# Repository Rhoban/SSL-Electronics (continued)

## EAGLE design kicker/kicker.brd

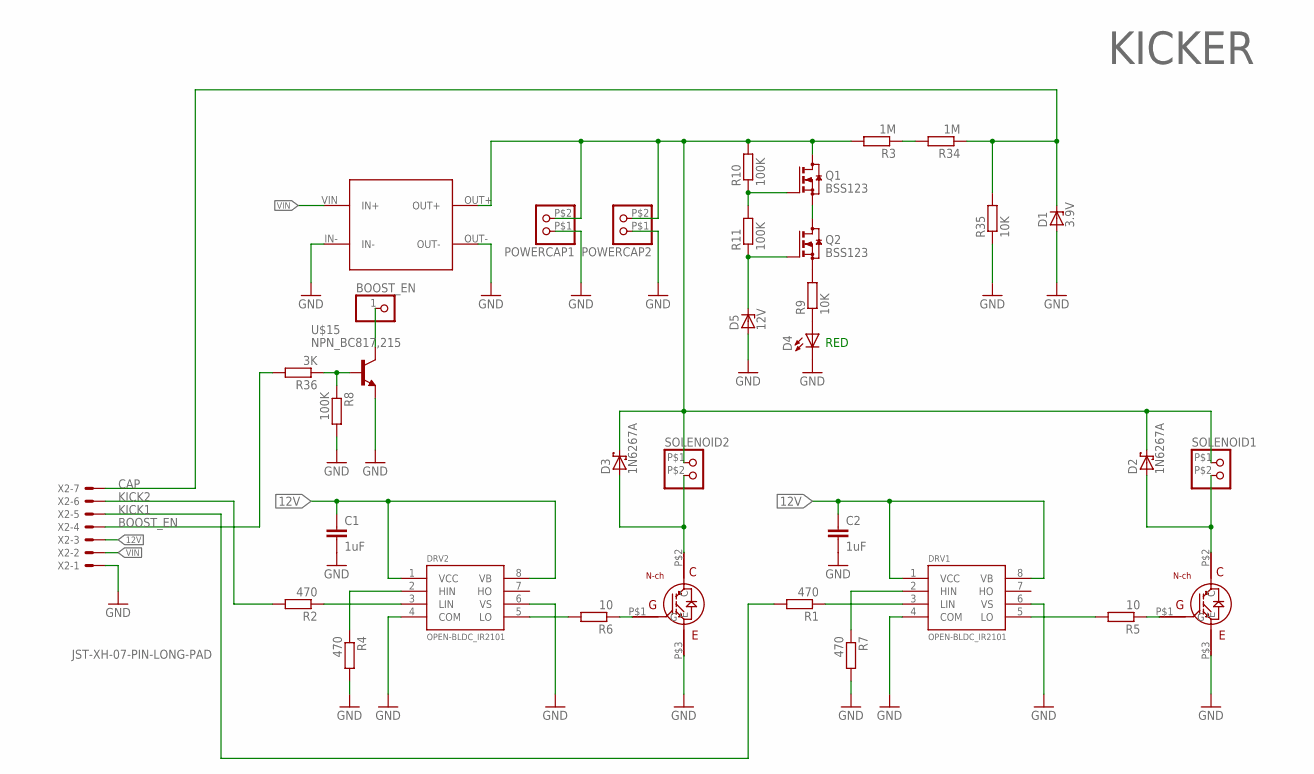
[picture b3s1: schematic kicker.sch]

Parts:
BOOST_EN: CONNEC_1X01
C1, C2: 1uF; C0805
D1: 3.9V; SOD80C; FARNELL 1097198
D2, D3: 1N6267A; C4111-15; FARNELL 9551735
D4: RED; LED-1206; FARNELL 1581233
D5: 12V; SOD80C; FARNELL 2319144
DRV1, DRV2: OPEN-BLDC_IR2101; OPEN-BLDC_SO-8; FARNELL 8638730
POWERCAP1, POWERCAP2: CONNEC_1X02BIG; CONNEC_1X02_BIG
Q1, Q2: BSS123; SOT23
R1, R2, R4, R7: 470; R0805; FARNELL 2446965
R3, R34: 1M; R0805; FARNELL 2129375
R5, R6: 10; R0805; FARNELL 2446965
R8: 100K; R0805; FARNELL 2446965
R9, R35: 10K; R0805; FARNELL 2447553
R10, R11: 100K; R0805; FARNELL 2447553
R36: 3K; R0805; FARNELL 2446965
SOLENOID1, SOLENOID2: CONNEC_1X02BIG; CONNEC_1X02_BIG
U$1, U$11: TO-247A; TO-247; FARNELL 2429705
U$5: BOOSTER; BOOSTER_390V
U$15: NPN_BC817,215; SOT-23; FARNELL 1081223
X2: JST-XH-07-PIN-LONG-PAD; JST-XH-07-PACKAGE-LONG-PAD

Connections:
12V: C1.1, C2.1, DRV1.1 (VCC), DRV1.8 (VB), DRV2.1 (VCC), DRV2.8 (VB), X2.3
BOOST_EN: R36.2, X2.4
CAP: D1.C, R34.1, R35.2, X2.7
GND: C1.2, C2.2, D1.A, D4.C, D5.A, DRV1.4 (COM), DRV1.6 (VS), DRV2.4 (COM), DRV2.6 (VS), POWERCAP1.P$1 (1), POWERCAP2.P$1 (1), R4.2, R7.2, R8.2, R35.1, U$1.P$3 (E), U$5.IN-, U$5.OUT-, U$11.P$3 (E), U$15.2 (E), X2.1
KICK1: R1.2, X2.5
KICK2: R2.2, X2.6
unnamed: DRV2.3 (LIN), R2.1
unnamed: D2.A, SOLENOID1.P$2 (2), U$1.P$2 (C)
unnamed: DRV2.5 (LO), R6.2
unnamed: R3.1, R34.2
unnamed: DRV1.3 (LIN), R1.1
unnamed: DRV2.2 (HIN), R4.1
unnamed: R5.1, U$1.P$1 (G)
unnamed: R6.1, U$11.P$1 (G)
unnamed: DRV1.5 (LO), R5.2
unnamed: Q2.2 (S), R9.2
unnamed: D4.A, R9.1
unnamed: Q1.2 (S), Q2.3 (D)
unnamed: DRV1.2 (HIN), R7.1
unnamed: Q1.1 (G), R10.1, R11.2
unnamed: D5.C, Q2.1 (G), R11.1
unnamed: D3.A, SOLENOID2.P$2 (2), U$11.P$2 (C)
unnamed: BOOST_EN.1, U$15.3 (C)
unnamed: R8.1, R36.1, U$15.1 (B)
VBOOST: D2.C, D3.C, POWERCAP1.P$2 (2), POWERCAP2.P$2 (2), Q1.3 (D), R3.2, R10.2, SOLENOID1.P$1 (1), SOLENOID2.P$1 (1), U$5.OUT+
VIN: U$5.VIN (IN+), X2.2

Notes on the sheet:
KICKER
RED

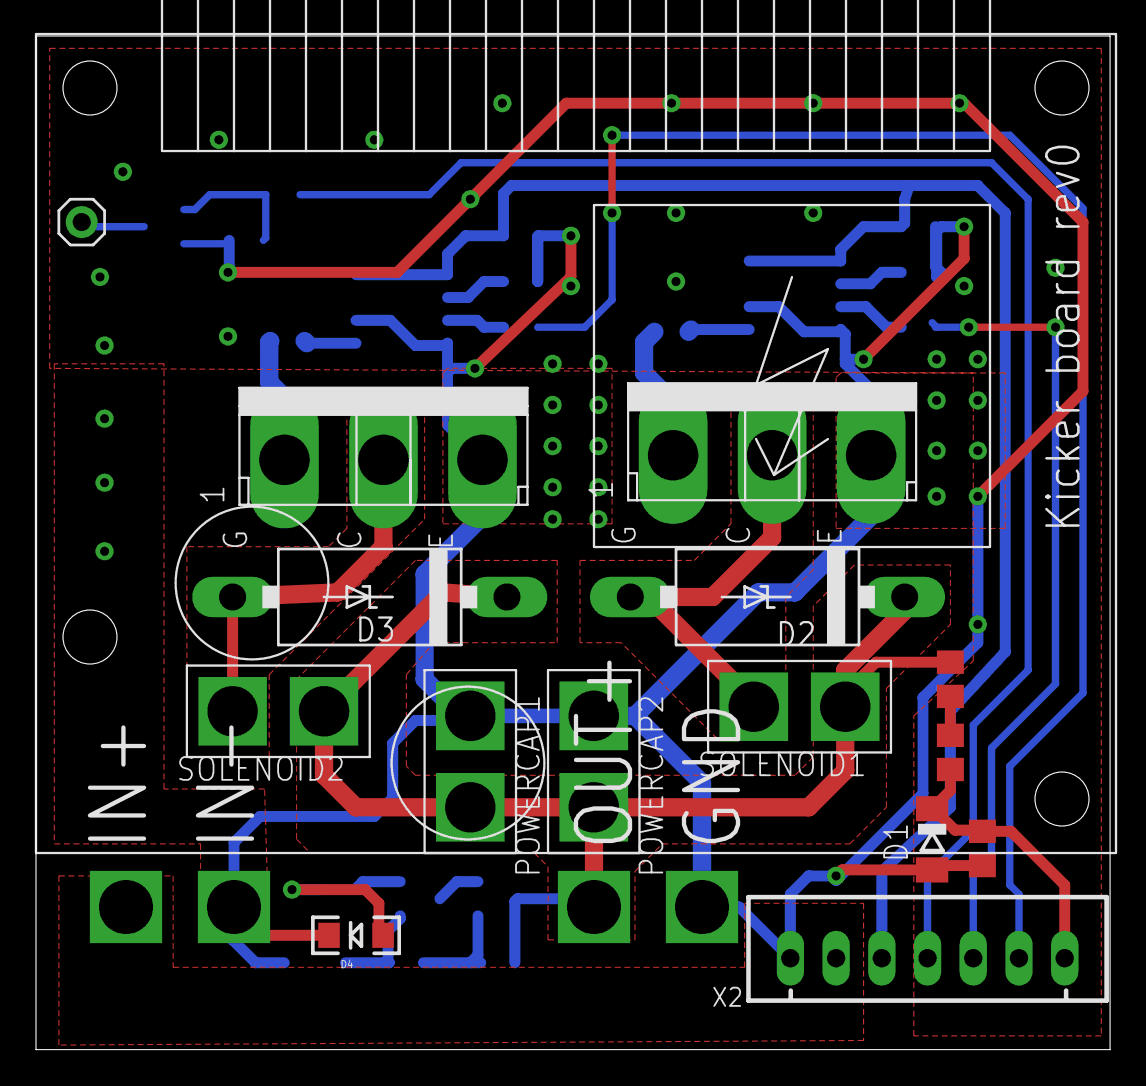
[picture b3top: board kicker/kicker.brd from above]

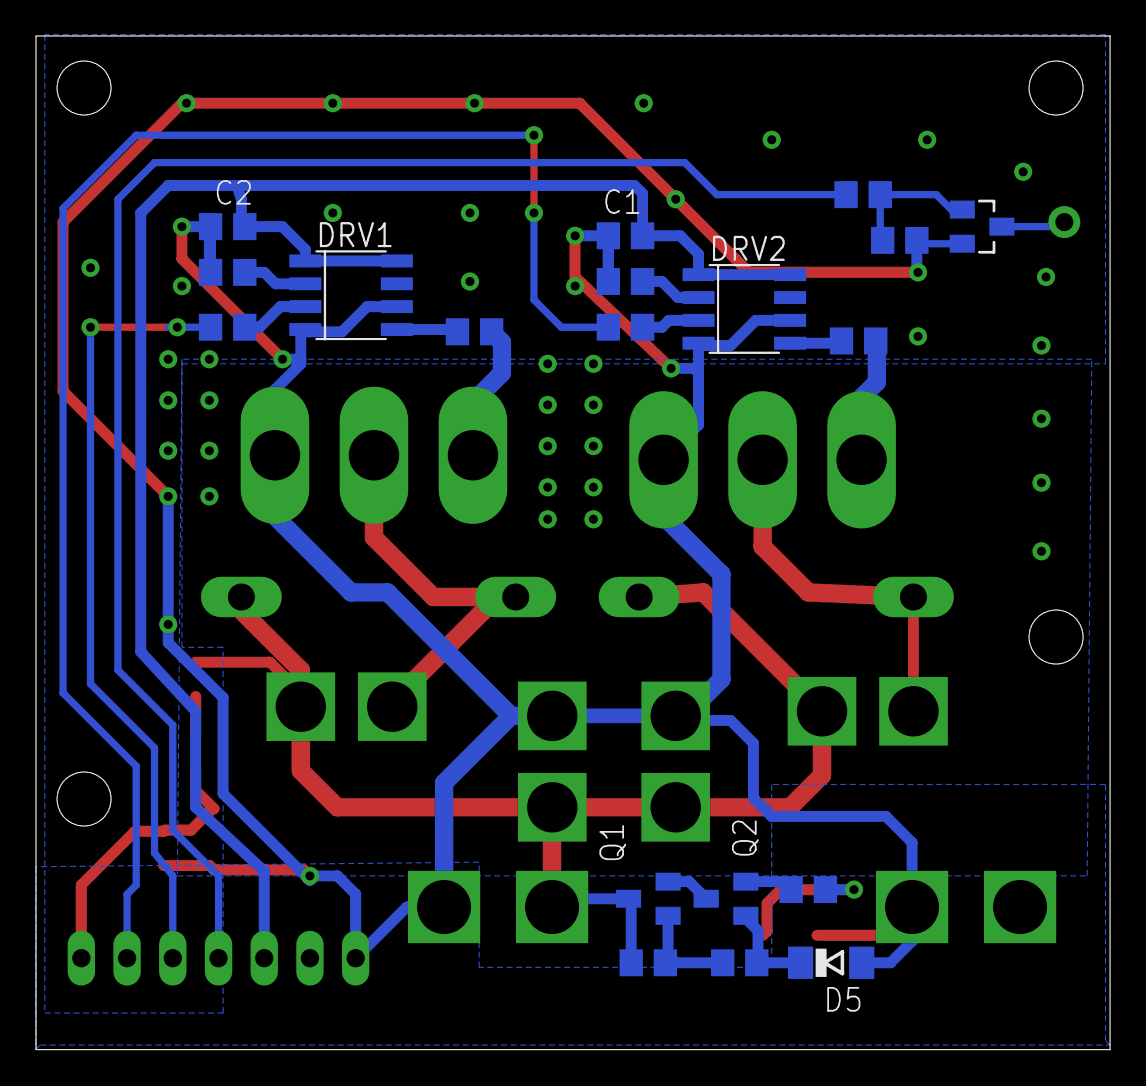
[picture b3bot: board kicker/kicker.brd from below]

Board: 2 copper layers, 59.7 x 56.3 mm, 35 parts (19 on the bottom side), 26 nets.

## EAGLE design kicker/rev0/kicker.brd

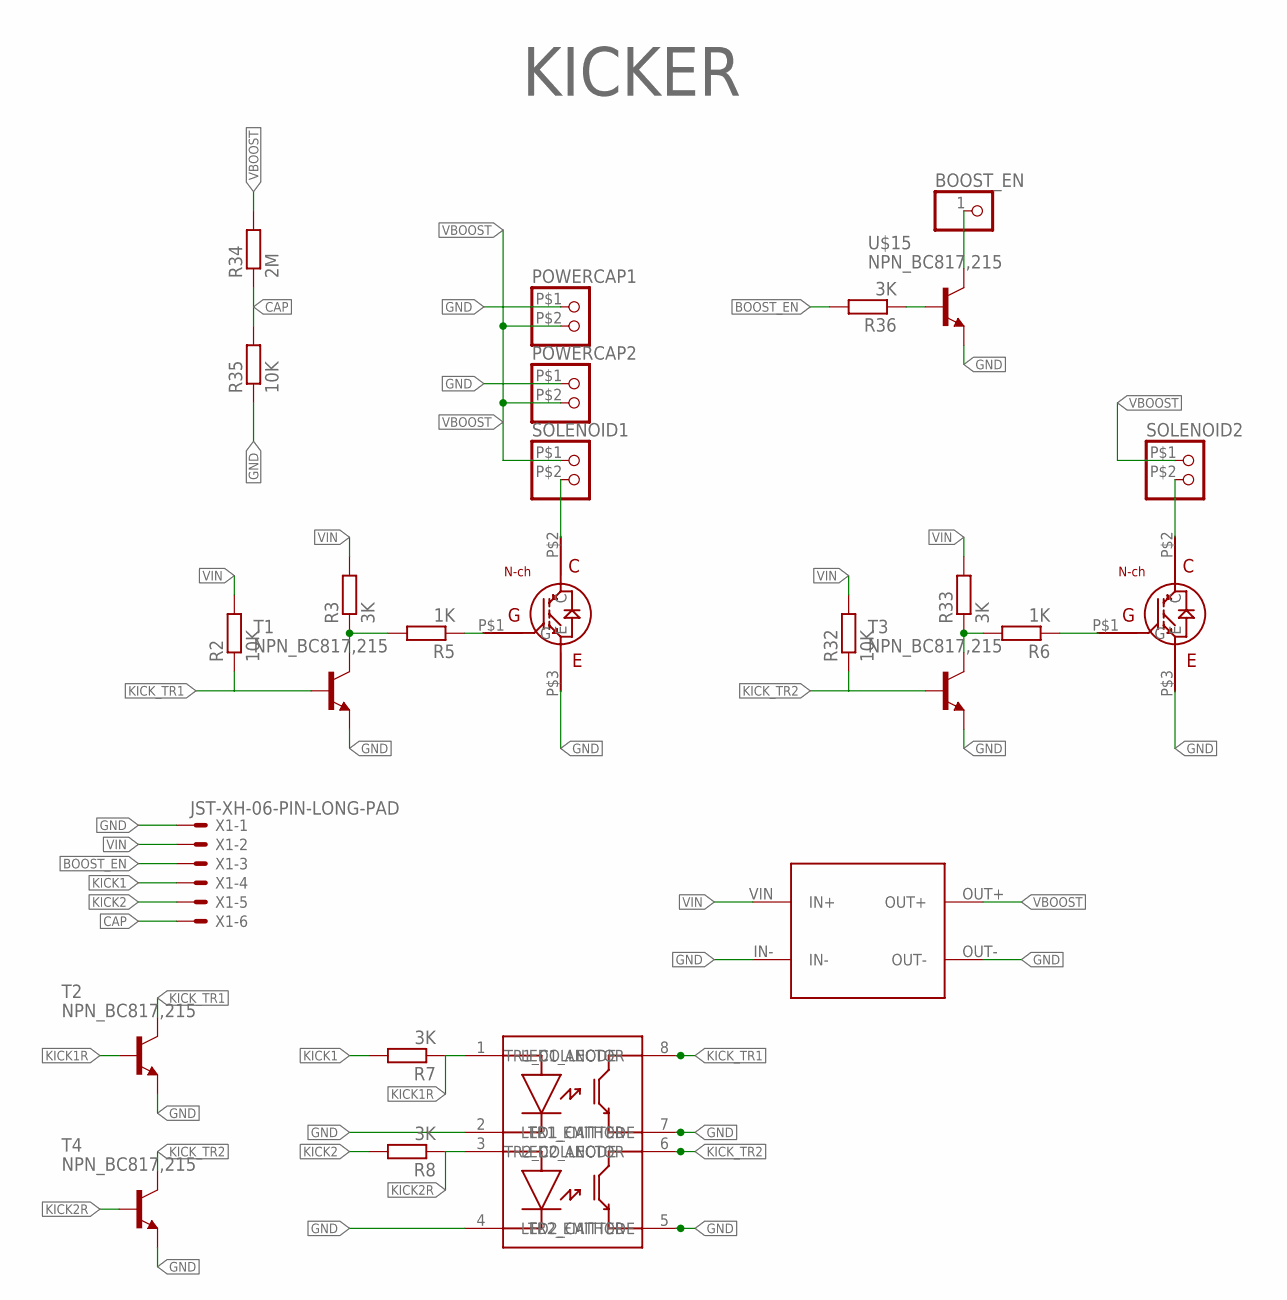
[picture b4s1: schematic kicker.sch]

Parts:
BOOST_EN: CONNEC_1X01
POWERCAP1, POWERCAP2: CONNEC_1X02BIG; CONNEC_1X02_BIG
R2, R32: 10K; R0805; FARNELL 2446965
R3, R7, R8, R33, R36: 3K; R0805; FARNELL 2446965
R5, R6: 1K; R0805; FARNELL 2446965
R34: 2M; R0805; FARNELL 2129375
R35: 10K; R0805; FARNELL 2447553
SOLENOID1, SOLENOID2: CONNEC_1X02BIG; CONNEC_1X02_BIG
T1, T2, T3, T4: NPN_BC817,215; SOT-23; FARNELL 1081223
U$1, U$11: TO-247A; TO-247; FARNELL 2429705
U$4: ACPL-227-500E; SO8; FARNELL 1634749RL
U$5: BOOSTER; BOOSTER_390V
U$15: NPN_BC817,215; SOT-23; FARNELL 1081223
X1: JST-XH-06-PIN-LONG-PAD; JST-XH-06-PACKAGE-LONG-PAD

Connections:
BOOST_EN: R36.2, X1.3
CAP: R34.1, R35.2, X1.6
GND: POWERCAP1.P$1 (1), POWERCAP2.P$1 (1), R35.1, T1.2 (E), T2.2 (E), T3.2 (E), T4.2 (E), U$1.P$3 (E), U$4.2 (LED1_CATHODE), U$4.4 (LED2_CATHODE), U$4.5 (TR2_EMITTER), U$4.7 (TR1_EMITTER), U$5.IN-, U$5.OUT-, U$11.P$3 (E), U$15.2 (E), X1.1
KICK1: R7.2, X1.4
KICK1R: R7.1, T2.1 (B), U$4.1 (LED1_ANODE)
KICK2: R8.2, X1.5
KICK2R: R8.1, T4.1 (B), U$4.3 (LED2_ANODE)
KICK_TR1: R2.1, T1.1 (B), T2.3 (C), U$4.8 (TR1_COLLECTOR)
KICK_TR2: R32.1, T3.1 (B), T4.3 (C), U$4.6 (TR2_COLLECTOR)
unnamed: SOLENOID1.P$2 (2), U$1.P$2 (C)
unnamed: R3.1, R5.2, T1.3 (C)
unnamed: R5.1, U$1.P$1 (G)
unnamed: R6.1, U$11.P$1 (G)
unnamed: R6.2, R33.1, T3.3 (C)
unnamed: SOLENOID2.P$2 (2), U$11.P$2 (C)
unnamed: BOOST_EN.1, U$15.3 (C)
unnamed: R36.1, U$15.1 (B)
VBOOST: POWERCAP1.P$2 (2), POWERCAP2.P$2 (2), R34.2, SOLENOID1.P$1 (1), SOLENOID2.P$1 (1), U$5.OUT+
VIN: R2.2, R3.2, R32.2, R33.2, U$5.VIN (IN+), X1.2

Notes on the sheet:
KICKER

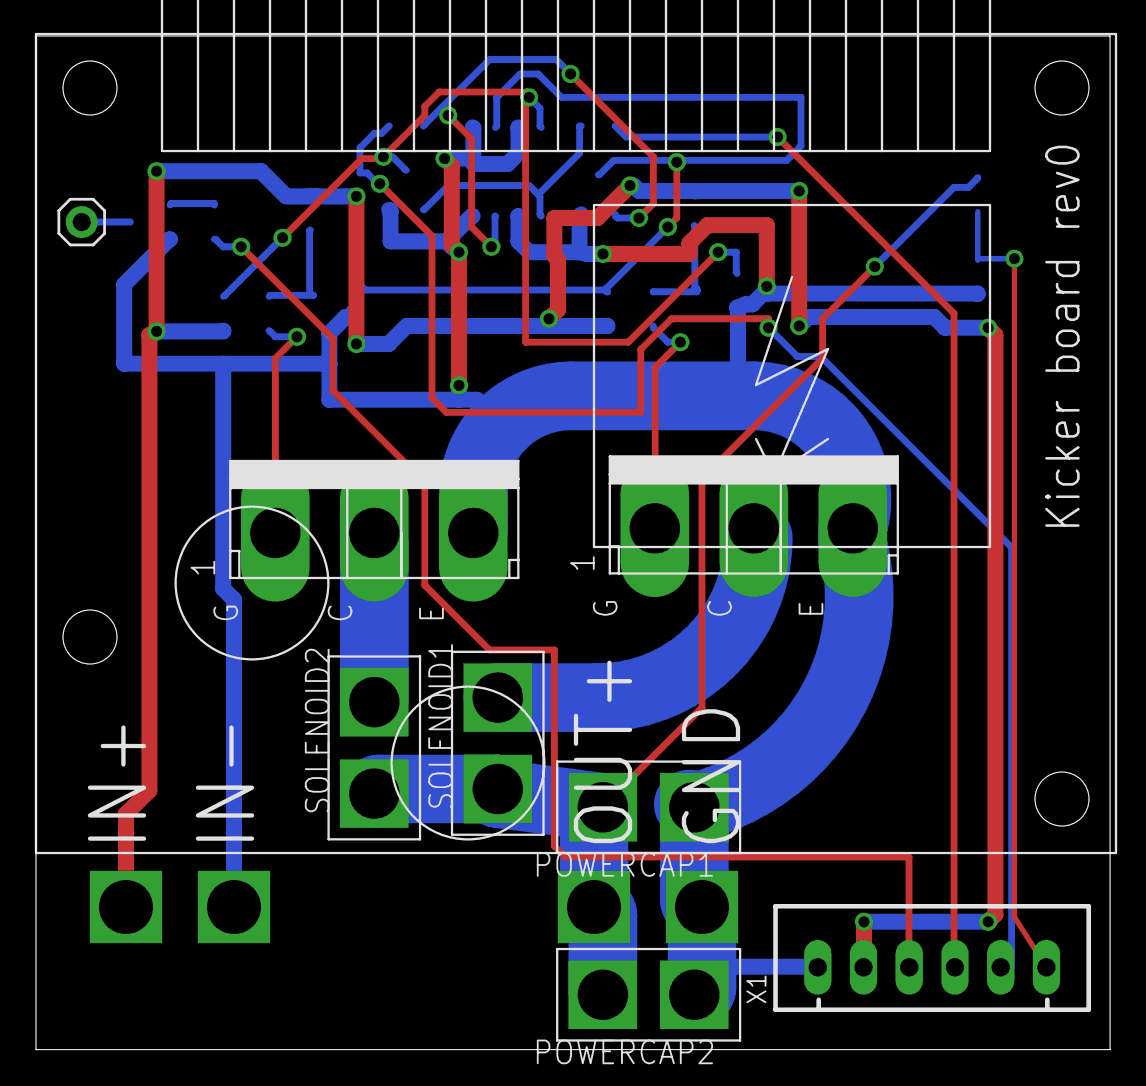
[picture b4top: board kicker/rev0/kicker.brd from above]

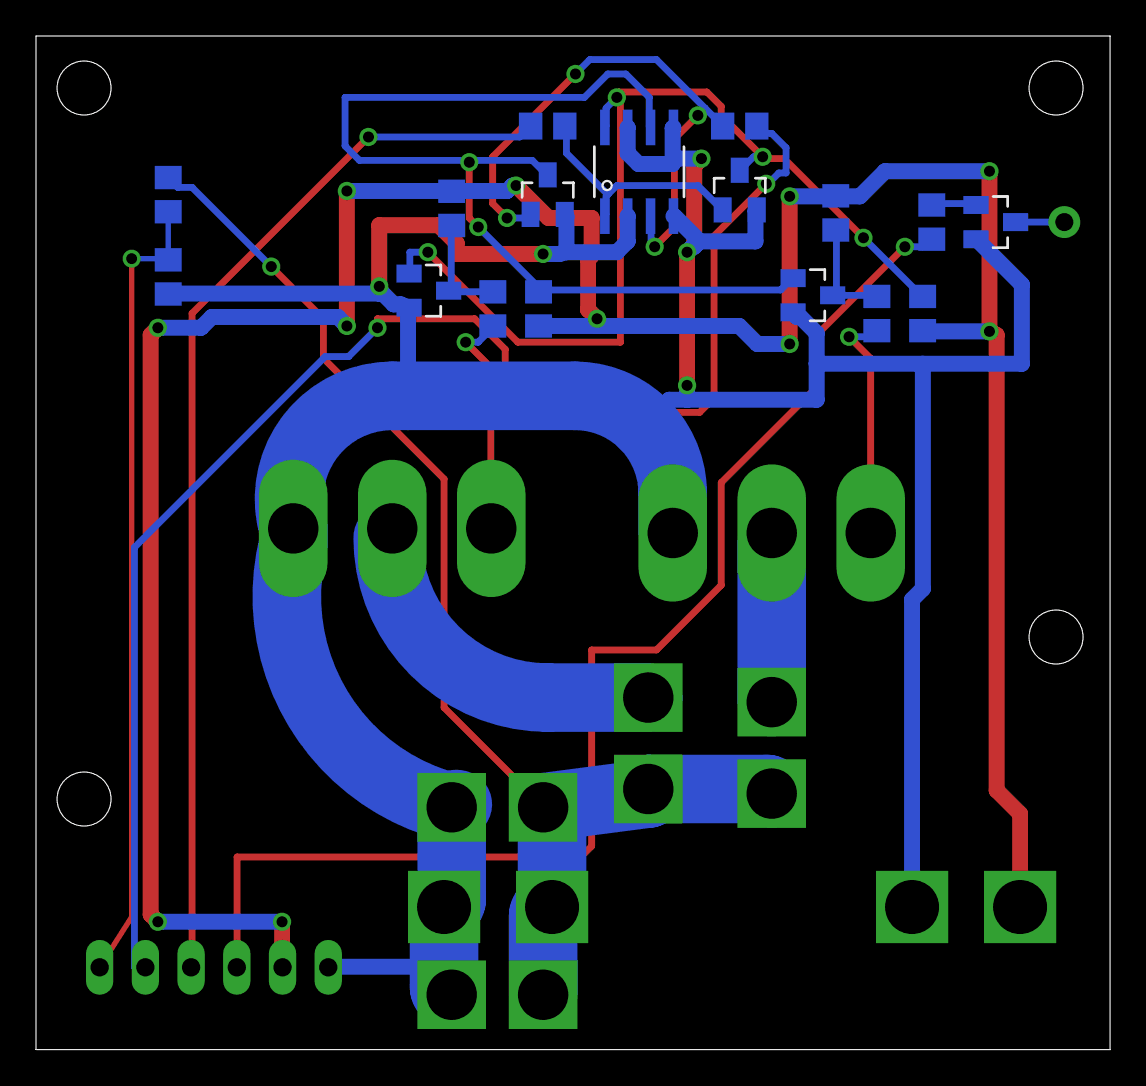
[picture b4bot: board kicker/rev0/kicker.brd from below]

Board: 2 copper layers, 59.7 x 56.3 mm, 26 parts (17 on the bottom side), 19 nets.

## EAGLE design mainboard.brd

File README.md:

# SSL Boards

## Compiling firmware

Be sure you follow the README.md from https://github.com/Rhoban/Maple/ to have the prerequisite.

You can clone the `Maple` repository, for instance in your home:

    git clone git@github.com:Rhoban/Maple.git

Then, go in the firmware directory (for instance in brushless or in mainboard) and make a symlink to it:

    ln -s $HOME/Maple Maple

You can then compile and install:

for master board:
    export COMPILE_MASTER=yes
    export BOOTLOADER_PORT=/dev/ttyACM0
    make clean
    make install

for robot board:
    export COMPILE_MASTER=no
    export BOOTLOADER_PORT=/dev/ttyACM0
    make clean
    make install

-------------------------------------------------

## Components

You can find most of the component source in the `FARNELL` attribute of each component.

### Main board

### Connectors

* JST-ZH 2 pin connector + cables
* JST-XH 7 pins connector for kicker board
* XT-60 connector (same as wire connector)

#### Maple mini

Board containing micro-controller (mainboard controller)

#### GY-85

9DOF IMU

#### nRF24L01 modules

2.4Ghz communication modules with short antenna (Farnell: 2143316)

### Screws

* M3 holes are on the board, on a 126x82mm rectangle.
* M3x10 spacers can be used to hold the drivers on the board

-------------------------------------------------

## Brushless driver

### Connectors

* JST-ZH 5 pin connector (for hall sensor)
* JST-ZH 6 pin connector (for encoder)
* JST-XH 3 pin connector (for motor phases)
  
-------------------------------------------------

## Kicker board

### Power capacitor

Power capacitors, current target is 2200uF / 200V (2102441)

### Flash brushless driver
first, add a udev rules in /etc/udev/rules.d/10-maple.rules 

ATTRS{idProduct}=="0003", ATTRS{idVendor}=="1eaf", MODE="0666", GROUP="plugdev" SYMLINK+="maple"

in brushless/firmware directory
   make
Then, with robot off and usb cable connected to driver (connector under the robot), enter the following command
just after plug-in:

dfu-util -a1 -d 1eaf:0003 -D build/maple.bin  -d /dev/maple

This is because driver remains in dfu only a short time after power up. If it fails, try again

### Connectors

* JST-XH 7 pins connector

#### Voltage booster

Can be easily found with keywords "390V booster"

### Screws

M3 spacers to fix the board

-------------------------------------------------

## Misc

#### Fuses

F447 fuses on the wire are used to protect

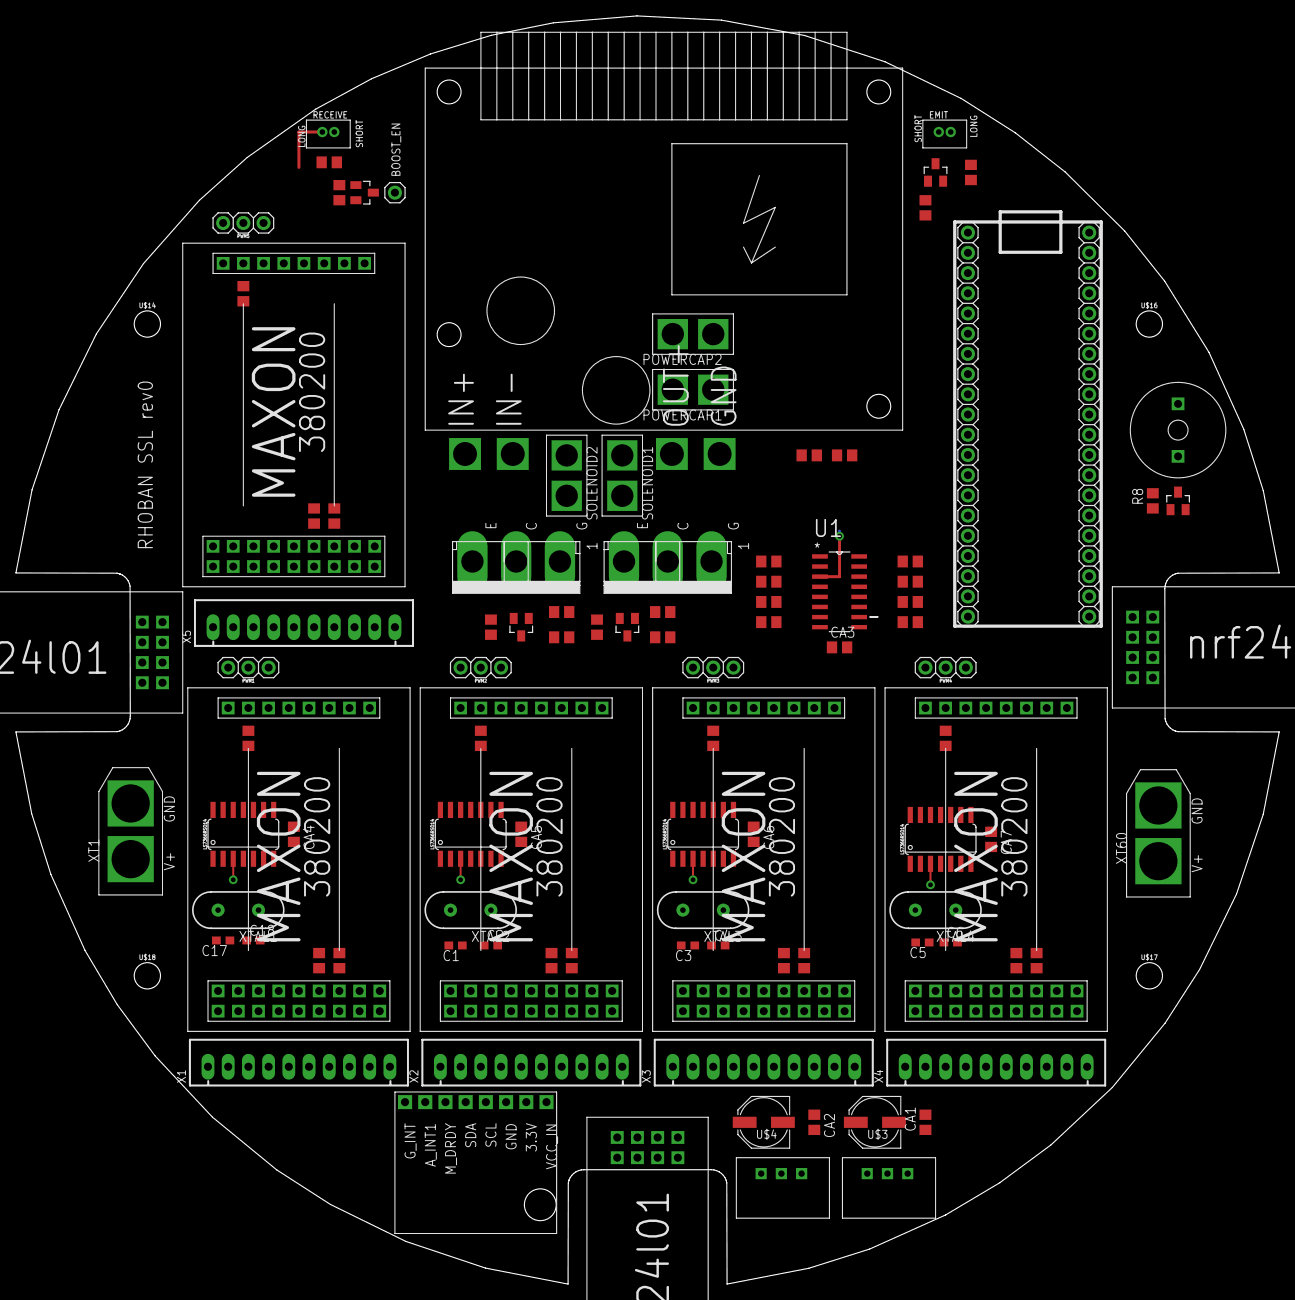
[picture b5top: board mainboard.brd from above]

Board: 2 copper layers, 158.8 x 159.4 mm, 106 parts (0 on the bottom side), 116 nets.

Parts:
BOOST_EN: CONNEC_1X01
C1, C2, C3, C4, C5, C6, C17, C18: 15pF; C0603
CA1, CA2, CA3, CA4, CA5, CA6, CA7: C_EU-100NF; C0805
COM1, COM2, COM3: NRF24L01
EMIT: CONNEC_1X02JST-ZH; JST_ZH_2P
ENC1, ENC2, ENC3, ENC4: LS7366RSO14; SO14
MAPLE: MAPLE_MINI; CONNEC_2X20
POWERCAP1, POWERCAP2: CONNEC_1X02BIG; CONNEC_1X02_BIG
PWM1, PWM2, PWM3, PWM4, PWM5: CONNEC_1X03
R1, R4, R16, R17, R19, R20, R22, R23, R25, R26, R28, R29, R31: 1K; R0805
R2, R3, R7, R8, R9, R10, R11, R12, R13, R14, R15, R32, R33, R36: 3K; R0805
R5: 110; R0805
R6, R35: 10K; R0805
R18, R21, R24, R27, R30: 24k; R0805
R34: 2M; R0805
RECEIVE: CONNEC_1X02JST-ZH; JST_ZH_2P
REG3.3V, REG5V: REG_5V; TRACOPOWER
SOLENOID1, SOLENOID2: CONNEC_1X02BIG; CONNEC_1X02_BIG
T1, T2, T3: NPN_BC817,215; SOT-23
U1: CD4051BM; SOIC127P600X175-16N
U$1, U$11: TO-247A; TO-247
U$2: GY-85
U$3, U$4: 47uF; PANASONIC_D
U$5: BOOSTER; BOOSTER_390V
U$6, U$7, U$8, U$9, U$10: MAXON380200
U$12, U$15: NPN_BC817,215; SOT-23
U$13: BUZZER66
U$14, U$16, U$17, U$18: STAND-OFF
X1, X2, X3, X4, X5: JST-XH-10-PIN-LONG-PAD; JST-XH-10-PACKAGE-LONG-PAD
XT1, XT60: CONNEC_ALIM; XT60
XTAL1, XTAL2, XTAL3, XTAL4: 40Mhz; HC49US

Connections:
3.3: CA1.1, CA3.1, COM1.CE, COM1.VCC, COM2.CE, COM2.VCC, COM3.CE, COM3.VCC, MAPLE.AV+, MAPLE.VCC, R2.2, R6.1, R7.1, R9.1, R10.1, R11.1, R12.1, R13.1, R14.1, R15.1, R32.2, REG3.3V.P$3, U1.16, U$2.3.3, U$3.+, U$13.P$2
BOOST_EN: MAPLE.X27, R36.2
BUZZER: MAPLE.X11, R8.2
CAP: MAPLE.X6, R34.1, R35.2
CS1: ENC1.4, R7.2, U1.13
CS2: ENC2.4, R9.2, U1.14
CS3: ENC3.4, R10.2, U1.15
CS4: ENC4.4, R11.2, U1.12
CS5: COM1.CSN, R12.2, U1.1
CS6: COM2.CSN, R13.2, U1.5
CS7: COM3.CSN, R14.2, U1.2
CS8: R15.2, U1.4
CSA1: MAPLE.X20, U1.11
CSA2: MAPLE.X21, U1.10
CSA3: MAPLE.X22, U1.9
GND: C1.1, C2.1, C3.1, C4.1, C5.1, C6.1, C17.1, C18.1, CA1.2, CA2.2, CA3.2, CA4.2, CA5.2, CA6.2, CA7.2, COM1.GND, COM2.GND, COM3.GND, ENC1.3, ENC2.3, ENC3.3, ENC4.3, MAPLE.AV-, MAPLE.GND, POWERCAP1.P$1, POWERCAP2.P$1, PWM1.1, PWM2.1, PWM3.1, PWM4.1, PWM5.1, R16.1, R18.1, R19.1, R21.1, R22.1, R24.1, R25.1, R27.1, R28.1, R30.1, R35.1, RECEIVE.P$2, T1.2, T2.2, T3.2, U1.3, U1.6, U1.7, U1.8, U$1.P$3, U$2.GND, U$3.-, U$4.-, U$5.IN-, U$5.OUT-, U$6.9, U$6.10, U$6.14, U$6.16, U$6.24, U$7.9, U$7.10, U$7.14, U$7.16, U$7.24, U$8.9, U$8.10, U$8.14, U$8.16, U$8.24, U$9.9, U$9.10, U$9.14, U$9.16, U$9.24, U$10.9, U$10.10, U$10.14, U$10.16, U$10.24, U$11.P$3, U$12.2, U$15.2, X1.4, X2.4, X3.4, X4.4, X5.4, XT1.GND, XT60.GND
IMU_SCL: MAPLE.X16, U$2.SCL
IMU_SDA: MAPLE.X15, U$2.SDA
INDEX: ENC1.10, ENC2.10, ENC3.10, ENC4.10, MAPLE.X26
IRQ1: COM1.IRQ, MAPLE.X23
IRQ2: COM2.IRQ, MAPLE.X24
IRQ3: COM3.IRQ, MAPLE.X25
IR_EMIT: MAPLE.X12, R4.1
IR_RECEIVE: MAPLE.X10, R6.2, RECEIVE.P$1
KICK1: MAPLE.X0, R1.1, R2.1
KICK2: MAPLE.X1, R31.1, R32.1
M1_A: ENC1.12, X1.9
M1_B: ENC1.11, X1.10
M1_DIR: MAPLE.X13, U$6.23
M1_HALL1: U$6.13, X1.6
M1_HALL2: U$6.15, X1.7
M1_HALL3: U$6.17, X1.8
M1_SPEED: MAPLE.X3, PWM1.3, U$6.26
M1_W1: U$6.1, U$6.2, X1.1
M1_W2: U$6.3, U$6.4, X1.2
M1_W3: U$6.5, U$6.6, X1.3
M2_A: ENC2.12, X2.9
M2_B: ENC2.11, X2.10
M2_DIR: MAPLE.X14, U$7.23
M2_HALL1: U$7.13, X2.6
M2_HALL2: U$7.15, X2.7
M2_HALL3: U$7.17, X2.8
M2_SPEED: MAPLE.X4, PWM2.3, U$7.26
M2_W1: U$7.1, U$7.2, X2.1
M2_W2: U$7.3, U$7.4, X2.2
M2_W3: U$7.5, U$7.6, X2.3
M3_A: ENC3.12, X3.9
M3_B: ENC3.11, X3.10
M3_DIR: MAPLE.X17, U$8.23
M3_HALL1: U$8.13, X3.6
M3_HALL2: U$8.15, X3.7
M3_HALL3: U$8.17, X3.8
M3_SPEED: MAPLE.X5, PWM3.3, U$8.26
M3_W1: U$8.1, U$8.2, X3.1
M3_W2: U$8.3, U$8.4, X3.2
M3_W3: U$8.5, U$8.6, X3.3
M4_A: ENC4.12, X4.9
M4_B: ENC4.11, X4.10
M4_DIR: MAPLE.X18, U$9.23
M4_HALL1: U$9.13, X4.6
M4_HALL2: U$9.15, X4.7
M4_HALL3: U$9.17, X4.8
M4_SPEED: MAPLE.X8, PWM4.3, U$9.26
M4_W1: U$9.1, U$9.2, X4.1
M4_W2: U$9.3, U$9.4, X4.2
M4_W3: U$9.5, U$9.6, X4.3
M5_DIR: MAPLE.X19, U$10.23
M5_HALL1: U$10.13, X5.6
M5_HALL2: U$10.15, X5.7
M5_SPEED: MAPLE.X9, PWM5.3, U$10.26
M5_W1: U$10.1, U$10.2, X5.1
M5_W2: U$10.3, U$10.4, X5.2
M5_W3: U$10.5, U$10.6, X5.3
MISO: COM1.MISO, COM2.MISO, COM3.MISO, ENC1.6, ENC2.6, ENC3.6, ENC4.6, MAPLE.X29
MOSI: COM1.MOSI, COM2.MOSI, COM3.MOSI, ENC1.7, ENC2.7, ENC3.7, ENC4.7, MAPLE.X28
MOTORS_EN: U$6.22, U$7.22, U$8.22, U$9.22, U$10.22
unnamed: R1.2, T1.1
unnamed: SOLENOID1.P$2, U$1.P$2
unnamed: R8.1, U$12.1
unnamed: R3.1, T1.3, U$1.P$1
unnamed: U$12.3, U$13.P$1
unnamed: EMIT.P$1, R5.2
unnamed: EMIT.P$2, T2.3
unnamed: R16.2, U$6.20
unnamed: R4.2, T2.1
unnamed: R17.2, U$6.21
unnamed: C1.2, ENC2.1, XTAL2.2
unnamed: C2.2, ENC2.2, XTAL2.1
unnamed: R19.2, U$7.20
unnamed: R18.2, U$6.25
unnamed: R31.2, T3.1
unnamed: R20.2, U$7.21
unnamed: C17.2, ENC1.1, XTAL1.2
unnamed: C18.2, ENC1.2, XTAL1.1
unnamed: R21.2, U$7.25
unnamed: C3.2, ENC3.1, XTAL3.2
unnamed: C4.2, ENC3.2, XTAL3.1
unnamed: R22.2, U$8.20
unnamed: R23.2, U$8.21
unnamed: R24.2, U$8.25
unnamed: C5.2, ENC4.1, XTAL4.2
unnamed: C6.2, ENC4.2, XTAL4.1
unnamed: R25.2, U$9.20
unnamed: R26.2, U$9.21
unnamed: R27.2, U$9.25
unnamed: R28.2, U$10.20
unnamed: R29.2, U$10.21
unnamed: R30.2, U$10.25
unnamed: R33.1, T3.3, U$11.P$1
unnamed: SOLENOID2.P$2, U$11.P$2
unnamed: BOOST_EN.1, U$15.3
unnamed: R36.1, U$15.1
SCK: COM1.SCK, COM2.SCK, COM3.SCK, ENC1.5, ENC2.5, ENC3.5, ENC4.5, MAPLE.X30
VBOOST: POWERCAP1.P$2, POWERCAP2.P$2, R34.2, SOLENOID1.P$1, SOLENOID2.P$1, U$5.OUT+
VCC: CA2.1, CA4.1, CA5.1, CA6.1, CA7.1, ENC1.14, ENC2.14, ENC3.14, ENC4.14, R17.1, R20.1, R23.1, R26.1, R29.1, REG5V.P$3, U$4.+, U$6.11, U$7.11, U$8.11, U$9.11, U$10.11, X1.5, X2.5, X3.5, X4.5, X5.5
VIN: R3.2, R5.1, R33.2, REG3.3V.P$1, REG5V.P$1, U$5.VIN, U$6.7, U$6.8, U$7.7, U$7.8, U$8.7, U$8.8, U$9.7, U$9.8, U$10.7, U$10.8, XT1.V+, XT60.V+

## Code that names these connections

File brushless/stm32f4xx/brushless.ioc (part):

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Mcu.Name=STM32F401R(B-C)Tx
Mcu.Package=LQFP64
Mcu.UserName=STM32F401RBTx
PA10.GPIOParameters=GPIO_Label
PA10.GPIO_Label=WPWM
PA10.Signal=S_TIM1_CH3
PA11.GPIOParameters=GPIO_Label
PA11.GPIO_Label=USB_DM
PA11.Mode=Device_Only
PA11.Signal=USB_OTG_FS_DM
PA12.GPIOParameters=GPIO_Label
PA12.GPIO_Label=USB_DP
PA12.Mode=Device_Only
PA12.Signal=USB_OTG_FS_DP
PA13.Mode=JTAG_4_pins
PA13.Signal=SYS_JTMS-SWDIO
PA14.Mode=JTAG_4_pins
PA14.Signal=SYS_JTCK-SWCLK
PA15.Mode=JTAG_4_pins
PA15.Signal=SYS_JTDI
PA5.Signal=S_TIM2_CH1_ETR
PA7.Signal=S_TIM3_CH2
PA8.GPIOParameters=GPIO_Label
PA8.GPIO_Label=UPWM
PA8.Signal=S_TIM1_CH1
PA9.GPIOParameters=GPIO_Label
PA9.GPIO_Label=VPWM
PA9.Signal=S_TIM1_CH2
PB1.GPIOParameters=GPIO_Label
PB1.GPIO_Label=LED
PB1.Signal=GPIO_Output
PB12.GPIOParameters=GPIO_Speed,PinState,GPIO_Label
PB12.GPIO_Label=ENC_INT_CS
PB12.GPIO_Speed=GPIO_SPEED_FREQ_VERY_HIGH
PB12.PinState=GPIO_PIN_SET
PB12.Signal=GPIO_Output
PB13.GPIOParameters=GPIO_Label
PB13.GPIO_Label=ENC_SCK
PB13.Mode=Full_Duplex_Master
PB13.Signal=SPI2_SCK
PB14.GPIOParameters=GPIO_Label
PB14.GPIO_Label=ENC_MISO
PB14.Mode=Full_Duplex_Master
PB14.Signal=SPI2_MISO
PB15.GPIOParameters=GPIO_Label
PB15.GPIO_Label=ENC_MOSI
PB15.Mode=Full_Duplex_Master
PB15.Signal=SPI2_MOSI
PB3.Mode=JTAG_4_pins
PB3.Signal=SYS_JTDO-SWO
PC0.GPIOParameters=GPIO_Label
PC0.GPIO_Label=I_U
PC0.Signal=ADCx_IN10
PC1.GPIOParameters=GPIO_Label
PC1.GPIO_Label=I_W
PC1.Signal=ADCx_IN11
PC14-OSC32_IN.Mode=LSE-External-Oscillator
PC14-OSC32_IN.Signal=RCC_OSC32_IN
PC15-OSC32_OUT.Mode=LSE-External-Oscillator
PC15-OSC32_OUT.Signal=RCC_OSC32_OUT
PC2.GPIOParameters=GPIO_Label
PC2.GPIO_Label=I_REF
PC2.Signal=ADCx_IN12
PC3.GPIOParameters=GPIO_Label
PC3.GPIO_Label=I_V
PC3.Signal=ADCx_IN13
PC6.GPIOParameters=GPIO_Label
PC6.GPIO_Label=UEN
PC6.Signal=GPIO_Output
PC7.GPIOParameters=GPIO_Label
PC7.GPIO_Label=VEN
PC7.Signal=GPIO_Output
PC8.GPIOParameters=GPIO_Label
PC8.GPIO_Label=WEN
PC8.Signal=GPIO_Output
PC9.GPIOParameters=GPIO_Speed,PinState,GPIO_Label
PC9.GPIO_Label=ENC_EXT_CS
PC9.GPIO_Speed=GPIO_SPEED_FREQ_VERY_HIGH
PC9.PinState=GPIO_PIN_SET
PC9.Signal=GPIO_Output
PH0\ -\ OSC_IN.Mode=HSE-External-Oscillator
PH0\ -\ OSC_IN.Signal=RCC_OSC_IN
PH1\ -\ OSC_OUT.Mode=HSE-External-Oscillator
PH1\ -\ OSC_OUT.Signal=RCC_OSC_OUT
RCC.HSE_VALUE=8000000
RCC.SYSCLKFreq_VALUE=84000000
RCC.SYSCLKSource=RCC_SYSCLKSOURCE_PLLCLK
board=custom

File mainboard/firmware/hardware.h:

#ifndef _HARDWARE_H
#define _HARDWARE_H

#include <stdint.h>

#define GREG 1
#define CATIE 2

#ifdef CATIE_BOARD
  #define BOARD CATIE
#endif
#ifdef GREG_BOARD
  #define BOARD GREG
#endif
#ifndef BOARD
  static_assert(false);
#endif

// Brushless drivers
#define DRIVERS_CS1 7
#define DRIVERS_CS2 1
#define DRIVERS_CS3 19
#define DRIVERS_CS4 18
#define DRIVERS_CS5 17

#define DRIVERS_SPI 1

// Multiplexer
#define MUX         8

#define ADDR1       14
#define ADDR2       31
#define ADDR3       2

// Communication pins
#define COM_CE1  13
#define COM_CE2  3
#define COM_CE3  9

#define COM_CS1 20
#define COM_CS2 21
#define COM_CS3 22

#define COM_IRQ1 23
#define COM_IRQ2 24
#define COM_IRQ3 0

#define COM_SPI 2

// Communication configuration
#define COM_ADDR   {0x22, 0x87, 0xe8, 0xf9, 0x00}
#define COM_MASTER 0xff

// Buzzer
#define BUZZER_PIN      11
#define BUZZER_TIMER    2

// Booster
#define BOOSTER_PIN     27
#define BOOSTER_TIMER   1
#define CAP_ADDR        4
#define CAP_R1          200000.0
#define CAP_R2          2000.0
#define CHARGE_CUR_ADDR 6
#define KICKER_CHARGING_VALUE 150.0

// Hall sensor
#define HALL1_ADDR      0
#define HALL2_ADDR      1
#define HALL3_ADDR      2
#define HALL4_ADDR      3

#define HALL_THRES     2000

// Kicker
#define KICKER1_PIN     25
#define KICKER2_PIN     26
#define KICKER_TIMER    4

// Voltage
#define BAT_ADDR        5
#define BAT_R1          10000
#define BAT_R2          1000

// Infrared
#define IR_EMIT         12
#define IR_RECEIVE      10
#define IR_THRESHOLD    600

void get_uid(uint8_t id[12]);

#endif

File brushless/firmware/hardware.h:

#ifndef _HARDWARE_H
#define _HARDWARE_H

#include "ssl.h"

// Flash address to write/read infos
#define INFO_FLASH_ADDR    0x0801FC00


// Defines the driver type (see below)
#define DRIVER_TYPE     TYPE_70W

#define TYPE_30W        1
#define TYPE_70W        2
#define TYPE_DRIBBLER   3

#ifndef DRIVER_TYPE
#error "You should set a value for DRIVER_TYPE"
#endif

// Encoder configuration
#if DRIVER_TYPE == TYPE_30W
#define ENCODER_QUADRATURE          // Quadrature encoder A/B
#define ENCODER_CPR      1024
#endif

#if DRIVER_TYPE == TYPE_70W
#define ENCODER_MAGNETIC            // Magnetic AS5048 14bit encoder
// #define ENCODER_CPR      1024
#define ENCODER_CPR      16384
// #define ENCODER_NONE                // No encoder
#endif

#if DRIVER_TYPE == TYPE_DRIBBLER
#define ENCODER_NONE                // No encoder
#endif

#define GREG 1
#define CATIE 2

#ifdef CATIE_BOARD
  #define BOARD CATIE
#endif
#ifdef GREG_BOARD
  #define BOARD GREG
#endif
#ifndef BOARD
  static_assert(false);
#endif

#if BOARD == CATIE
  #define REVERSE_HALL_PHASE
  // For SPI based encoders
  #define ENCODER_SPI         2
  #define ENCODER_SELECT_PIN  PB12
  #define ENCODER_SELECT_PIN_2  PC9
  #define ENCODER_INDEX_PIN   12 // Used to make a shift bit to define PB12

  // Current sensing
  #define CURRENT_U_PIN      PC0
  #define CURRENT_V_PIN      PC3
  #define CURRENT_W_PIN      PC1
  #define CURRENT_REF_PIN      PC2

  // Motors pins

  #ifdef REVERSE_PHASE
      #define U_SD_PIN       PC6  //use Timer 1 (Maple)
      #define U_IN_PIN       PA8  //use Timer 1 (Maple)

      #define V_SD_PIN       PC8  //use Timer 1 (Maple)
      #define V_IN_PIN       PA10  //use Timer 1 (Maple)

#define W_SD_PIN       PC7 //use Timer 1 (Maple)
#define W_IN_PIN       PA9 //use Timer 1 (Maple)
  #else
      #define U_SD_PIN       PC6 //use Timer 1 (Maple)
      #define U_IN_PIN       PA8 //use Timer 1 (Maple)

      #define V_SD_PIN       PC7 //use Timer 1 (Maple)
      #define V_IN_PIN       PA9 //use Timer 1 (Maple)

      #define W_SD_PIN       PC8  //use Timer 1 (Maple)
      #define W_IN_PIN       PA10 //use Timer 1 (Maple)
  #endif



  #ifdef REVERSE_HALL_PHASE
    #define HALLU_PIN        PA0
    #define HALLW_PIN        PA1
    #define HALLV_PIN        PA2
  #else
    #define HALLU_PIN        PA0
    #define HALLV_PIN        PA1
    #define HALLW_PIN        PA2
  #endif

  // SPI slave pin
  #define SLAVE_SPI           1
  #define SLAVE_PIN PA4
  #define SLAVE_CLK_PIN PA5
  #define SLAVE_MISO_PIN PA6
  #define SLAVE_MOSI_PIN PA7

  // Board LED pin
  #define LED_PIN     PB1
#endif

#if BOARD == GREG
  // For SPI based encoders
  #define ENCODER_SPI         2
  #define ENCODER_SELECT_PIN  31
  #define ENCODER_INDEX_PIN   12

  // Current sensing
  #define CURRENT_PIN      4

  // Motors pins

  #ifdef REVERSE_PHASE
      #define U_SD_PIN        10  //use Timer 2 (Maple Mini)
      #define U_IN_PIN       11  //use Timer 2 (Maple Mini)

      #define V_SD_PIN        33  //use Timer 3 (Maple Mini)
      #define V_IN_PIN       3  //use Timer 2 (Maple Mini)

#define W_SD_PIN        8 //use Timer 2 (Maple Mini)
#define W_IN_PIN       9 //use Timer 2 (Maple Mini)
  #else
      #define U_SD_PIN        10 //use Timer 2 (Maple Mini)
      #define U_IN_PIN       11 //use Timer 2 (Maple Mini)

      #define V_SD_PIN        8 //use Timer 2 (Maple Mini)
      #define V_IN_PIN       9 //use Timer 2 (Maple Mini)

      #define W_SD_PIN        33  //use Timer 3 (Maple Mini)
      #define W_IN_PIN       3 //use Timer 2 (Maple Mini)
  #endif


  #ifdef REVERSE_HALL_PHASE
    #define HALLU_PIN        7
    #define HALLW_PIN        6
    #define HALLV_PIN        5
  #else
    #define HALLU_PIN        7
    #define HALLV_PIN        6
    #define HALLW_PIN        5
  #endif

  // SPI slave pin
  #define SLAVE_SPI           1
  #define SLAVE_PIN           20

  // Board LED pin
  #define LED_PIN     22
  //#define LED_PIN     PB1



//  // For SPI based encoders
//  #define ENCODER_SPI         2
//  #define ENCODER_SELECT_PIN  PB12
//  #define ENCODER_INDEX_PIN   12 // Used to make a shift bit to define PB12
//
//  // Current sensing
//  #define CURRENT_PIN      PA7
//
//  // Motors pins
//
//  #ifdef REVERSE_PHASE
//      #define U_SD_PIN       PA1  //use Timer 2 (Maple Mini)
//      #define U_IN_PIN       PA0  //use Timer 2 (Maple Mini)
//
//      #define V_SD_PIN       PB1  //use Timer 3 (Maple Mini)
//      #define V_IN_PIN       PB0  //use Timer 2 (Maple Mini)
//
//      #define W_SD_PIN       PA3 //use Timer 2 (Maple Mini)
//      #define W_IN_PIN       PA2 //use Timer 2 (Maple Mini)
//  #else
//      #define U_SD_PIN       PA1 //use Timer 2 (Maple Mini)
//      #define U_IN_PIN       PA0 //use Timer 2 (Maple Mini)
//
//      #define V_SD_PIN       PA3 //use Timer 2 (Maple Mini)
//      #define V_IN_PIN       PA2 //use Timer 2 (Maple Mini)
//
//      #define W_SD_PIN       PB1  //use Timer 3 (Maple Mini)
//      #define W_IN_PIN       PB0 //use Timer 2 (Maple Mini)
//  #endif
//
//
//
//  #define HALLU_PIN        PA4
//  #define HALLV_PIN        PA5
//  #define HALLW_PIN        PA6
//
//  // SPI slave pin
//  #define SLAVE_SPI           1
//  #define SLAVE_PIN BOARD_JTDI_PIN
//
//  // Board LED pin
//  #define LED_PIN BOARD_JTMS_SWDIO_PIN
#endif



// Servo configuration
#define SPEED_DT    10
#define SERVO_DT    1

// Current protection
#define CURRENT_LIMIT       2.5
#define CURRENT_DURATION    500
#define CURRENT_MAX         8

#define MAX_MOTOR_VOLTAGE 12
#define HALF_MAX_MOTOR_VOLTAGE MAX_MOTOR_VOLTAGE/2

// XXX: Limiting PWM
#if DRIVER_TYPE == TYPE_70W
//#define CURRENT_DISABLE
#define PWM_MIN_PERCENT 0
#define PWM_MAX_PERCENT 95
#endif

#if DRIVER_TYPE == TYPE_30W
#define PWM_MIN_PERCENT 20
#define PWM_MAX_PERCENT 83
#endif

#if DRIVER_TYPE == TYPE_DRIBBLER
#define PWM_MIN_PERCENT 0
#define PWM_MAX_PERCENT 90
#endif

static_assert(0<=PWM_MIN_PERCENT, "");
static_assert(PWM_MIN_PERCENT<PWM_MAX_PERCENT, "");
static_assert(PWM_MAX_PERCENT<100, "");


// Limitting acceleration
#define ACC_MAX             10      // turn/s^2

#endif
